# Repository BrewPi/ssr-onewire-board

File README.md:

ssr-onewire-board
=================

ssr-onewire-board

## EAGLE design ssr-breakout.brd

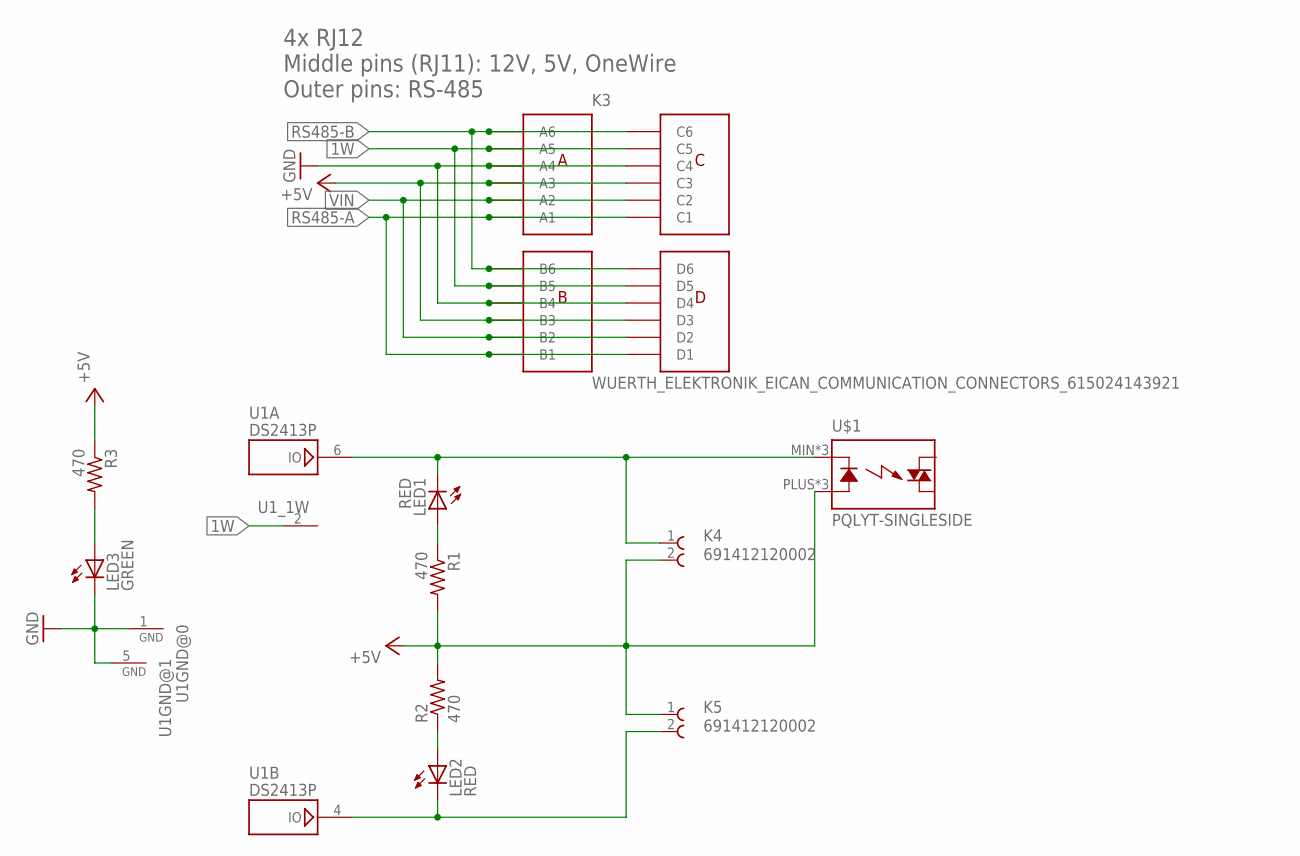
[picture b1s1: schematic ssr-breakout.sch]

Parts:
K3: WUERTH_ELEKTRONIK_EICAN_COMMUNICATION_CONNECTORS_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; WUERTH_ELEKTRONIK_EICAN_COMMUNICATION_CONNECTORS_6150241439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
K4, K5: 691412120002
LED1, LED2: RED; SPARKFUN-LED_LED-1206
LED3: GREEN; SPARKFUN-LED_LED-1206
R1, R2, R3: 470; R0805
U1: DS2413P; TSOC6
U$1: PQLYT-SINGLESIDE; PQLYT-PADS-ONLY

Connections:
1W: K3.A5, K3.B5, K3.C5, K3.D5, U1.2 (1W)
+5V: K3.A3, K3.B3, K3.C3, K3.D3, K4.2, K5.1, R1.2, R2.2, R3.1, U$1.PLUS (A), U$1.PLUSBOTTOM (A), U$1.PLUSTOP (A)
GND: K3.A4, K3.B4, K3.C4, K3.D4, LED3.C, U1.1 (GND), U1.5 (GND)
unnamed: K4.1, LED1.C, U1.6 (IO), U$1.MIN (K), U$1.MINBOTTOM (K), U$1.MINTOP (K)
unnamed: LED1.A, R1.1
unnamed: LED2.A, R2.1
unnamed: K5.2, LED2.C, U1.4 (IO)
unnamed: LED3.A, R3.2
RS485-A: K3.A1, K3.B1, K3.C1, K3.D1
RS485-B: K3.A6, K3.B6, K3.C6, K3.D6
VIN: K3.A2, K3.B2, K3.C2, K3.D2

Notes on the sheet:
4x RJ12 Middle pins (RJ11): 12V, 5V, OneWire Outer pins: RS-485

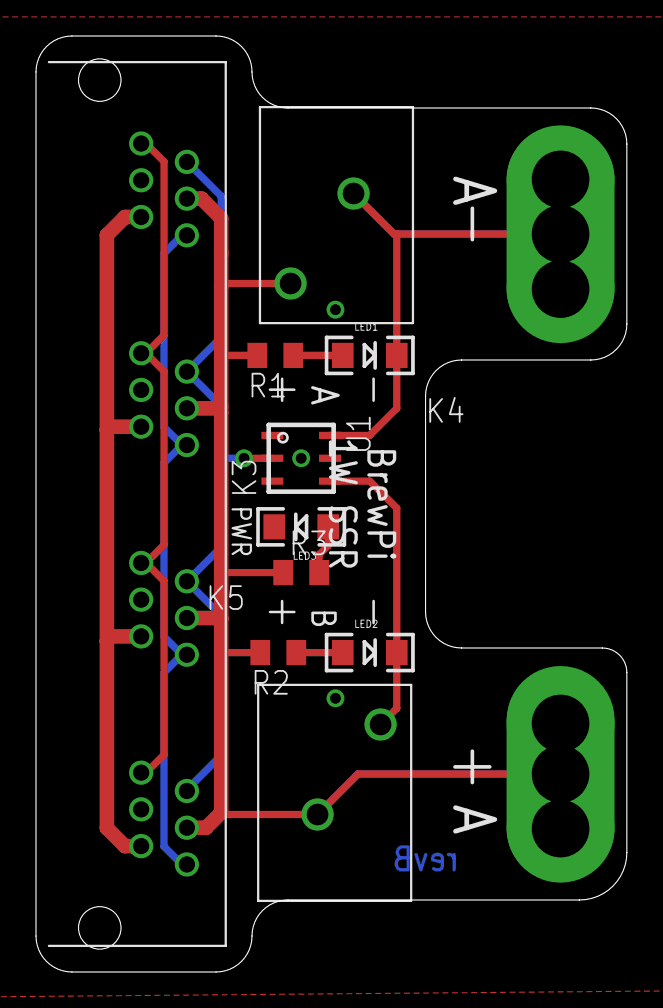
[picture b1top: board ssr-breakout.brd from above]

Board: 2 copper layers, 32.8 x 52.0 mm, 11 parts (0 on the bottom side), 11 nets.

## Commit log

2014-03-05 Initial commit of DS2413 OneWire breakout board. Please ignore AC side. This board attaches to 1 SSR to control it with the DS2413, a OneWire dual switch. Each output has a signal LED. A jumper conne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
2017-05-13 Small updates to layout to fit PQLYT SSR

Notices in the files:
parts and their libraries:
Wuerth_Elektronik_eiCan_Terminal_Blocks_: Copyright: Würth Elektronik
